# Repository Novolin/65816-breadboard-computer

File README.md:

# 65816-breadboard-computer
My Personal 65C816 breadboard build, including schematics, etc.

/KiCad contains my schematics/raw kicad files, if you want to laugh at my design.

/Software contains the programs I've written, mostly raw assembly, but I will hopefully have a C compiler up and running eventually.

/Docs will have a variety of documents on the exact nature of each hardware decision and how it works. I'll also be publishing these to a blog on my web zone. 

# Hardware Description:

This system is designed to use modular components, with room for expansion in RAM or I/O, using programmable logic. 

The primary CPU is a W65C816, which handles all logic/program execution. The "Bare Minimum" setup includes 32k of RAM and 32K of ROM space, both of which are placed on the primary controller board. The CPU is driven to 1 MHz by a divided clock oscillator, which provides a 2-phase clock signal, for any devices that may need it.

Expansion is handled through a 2x20 pin slot, so I can use a standard floppy drive cable to send it to a breakout board or other device.

## Graphical Output:

Despite my original intentions to use a z80 to drive a 320x240 display via weird magic bullshit, I have decided to switch to having the CPU directly control the display via the VIA's PORTB, though I will be sharing this with the 16x2 LCD thanks to some Ideas about how to handle I/O. See Docs/Displays for details.

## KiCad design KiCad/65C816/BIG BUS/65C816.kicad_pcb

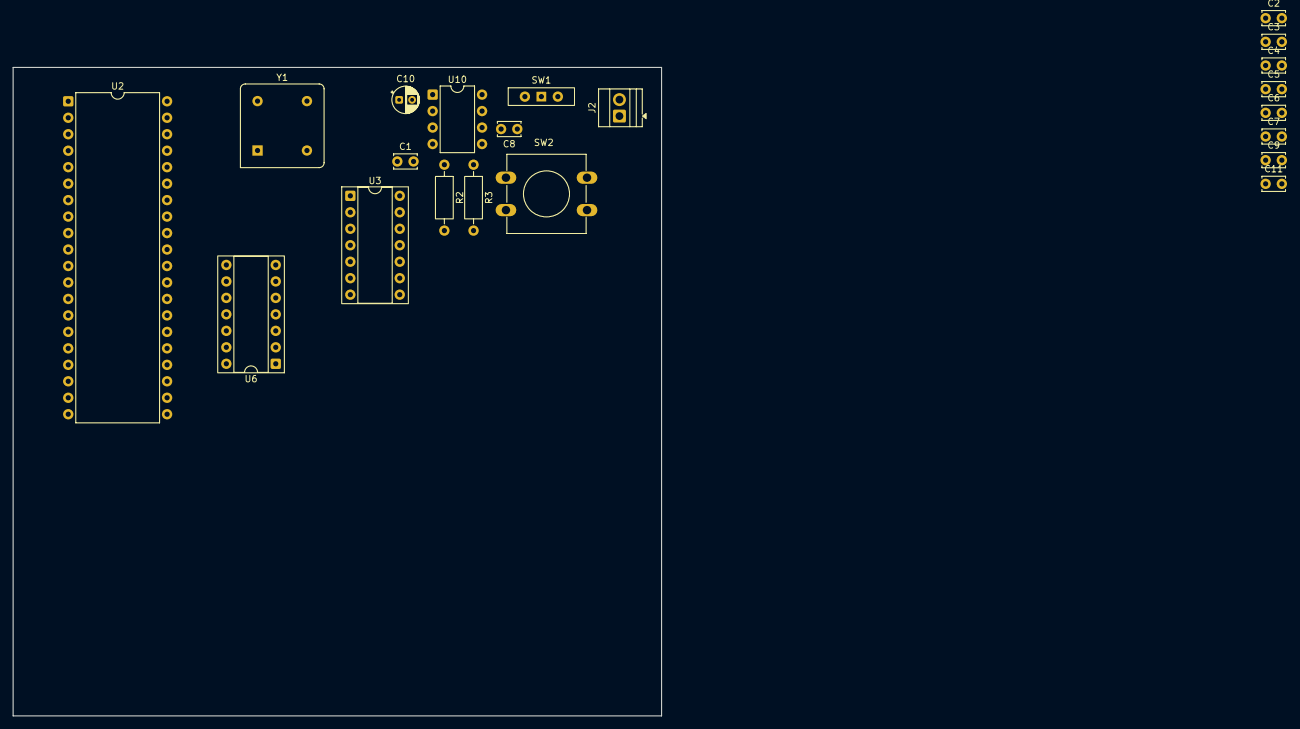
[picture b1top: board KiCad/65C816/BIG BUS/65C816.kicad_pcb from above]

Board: 2 copper layers, 100.0 x 100.0 mm, 21 parts (0 on the bottom side), 16 nets, no tracks yet.

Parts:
C1, C2, C3, C4, C5, C6, C7, C8, C9, C11: .1u; C_Disc_D3.4mm_W2.1mm_P2.50mm
C10: 2u; CP_Radial_D4.0mm_P2.00mm
J2: PWR IN; TerminalBlock_Xinya_XY308-2.54-2P_1x02_P2.54mm_Horizontal
R2: 10k; R_Axial_DIN0207_L6.3mm_D2.5mm_P10.16mm_Horizontal
R3: 1k; R_Axial_DIN0207_L6.3mm_D2.5mm_P10.16mm_Horizontal
SW1: PWR_SW; SW_Slide-03_Wuerth-WS-SLTV_10x2.5x6.4_P2.54mm
SW2: RESET; SW_PUSH-12mm
U2: W65C816SxP; DIP-40_W15.24mm
U3, U6: 74HC74; DIP-14_W7.62mm_Socket
U10: NE555P; DIP-8_W7.62mm
Y1: 16MHz; Oscillator_DIP-8

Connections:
+5V: C1.1, C2.1, C3.1, C4.1, C5.1, C6.1, C7.1, C9.1, C11.1, R2.2, R3.2, SW1.1 (B), U2.3 (~ABORT), U2.8 (VDD), U3.1 (~R), U3.4 (~S), U3.10 (~S), U3.13 (~R), U3.14 (VCC), U6.1 (~R), U6.4 (~S), U6.10 (~S), U6.13 (~R), U6.14 (VCC), U10.4 (R), U10.8 (VCC), Y1.1 (EN), Y1.8 (Vcc)
/CLK: U2.37 (ϕ0), U6.9 (Q)
/~CLK: U6.8 (~Q), U6.12 (D)
/~RESET: U2.40 (~RES), U10.3 (Q)
GND: C1.2, C2.2, C3.2, C4.2, C5.2, C6.2, C7.2, C8.1, C9.2, C10.2, C11.2, J2.1, SW2.1, U2.21 (VSS), U3.7 (GND), U6.7 (GND), U10.1 (GND), Y1.4 (GND)
unnamed: J2.2, SW1.3 (A)
unnamed: U3.3 (C), Y1.5 (OUT)
unnamed: U3.2 (D), U3.6 (~Q)
unnamed: U3.5 (Q), U3.11 (C)
unnamed: U3.8 (~Q), U3.12 (D)
unnamed: U3.9 (Q), U6.3 (C)
unnamed: U6.2 (D), U6.6 (~Q)
unnamed: U6.5 (Q), U6.11 (C)
unnamed: C8.2, U10.5 (CV)
unnamed: C10.1, R3.1, U10.6 (THR), U10.7 (DIS)
unnamed: R2.1, SW2.2, U10.2 (TR)

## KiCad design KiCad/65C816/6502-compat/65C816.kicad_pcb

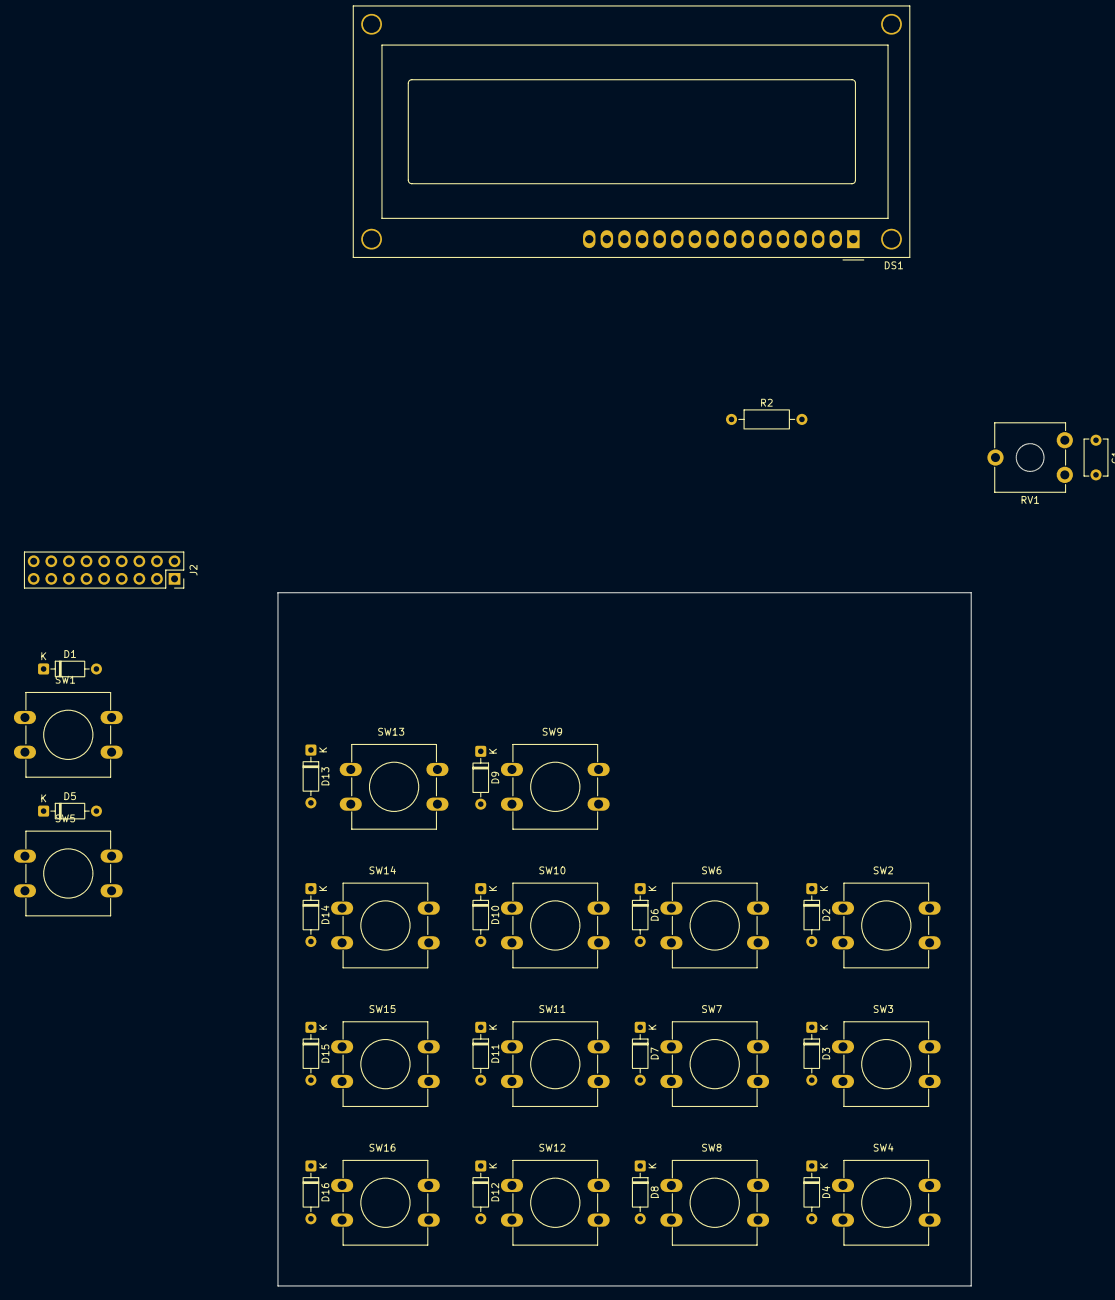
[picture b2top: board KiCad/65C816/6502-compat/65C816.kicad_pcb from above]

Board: 2 copper layers, 100.0 x 100.0 mm, 37 parts (0 on the bottom side), 35 nets, no tracks yet.

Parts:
C1: .1u; C_Disc_D5.1mm_W3.2mm_P5.00mm
D1, D2, D3, D4, D5, D6, D7, D8, D9, D10, D11, D12, D13, D14, D15, D16: D; D_DO-35_SOD27_P7.62mm_Horizontal
DS1: WC1602A
J2: Conn_02x09_Top_Bottom; PinSocket_2x09_P2.54mm_Vertical
R2: 680; R_Axial_DIN0207_L6.3mm_D2.5mm_P10.16mm_Horizontal
RV1: 1M; Potentiometer_ACP_CA9-V10_Vertical_Hole
SW1: A1; SW_PUSH-12mm
SW2: B1; SW_PUSH-12mm
SW3: C1; SW_PUSH-12mm
SW4: D1; SW_PUSH-12mm
SW5: A2; SW_PUSH-12mm
SW6: B2; SW_PUSH-12mm
SW7: C2; SW_PUSH-12mm
SW8: D2; SW_PUSH-12mm
SW9: A3; SW_PUSH-12mm
SW10: B3; SW_PUSH-12mm
SW11: C3; SW_PUSH-12mm
SW12: D3; SW_PUSH-12mm
SW13: A4; SW_PUSH-12mm
SW14: B4; SW_PUSH-12mm
SW15: C4; SW_PUSH-12mm
SW16: D4; SW_PUSH-12mm

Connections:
+5V: C1.2, DS1.2 (VDD), DS1.15 (LED(+)), J2.10, RV1.3
GND: C1.1, DS1.1 (VSS), J2.1, R2.1, RV1.1
unnamed: D1.2 (A), SW1.2
unnamed: D1.1 (K), D5.1 (K), D9.1 (K), D13.1 (K), J2.6
unnamed: D2.2 (A), SW2.2
unnamed: D3.2 (A), SW3.2
unnamed: D4.2 (A), SW4.2
unnamed: D5.2 (A), SW5.2
unnamed: D6.2 (A), SW6.2
unnamed: D7.2 (A), SW7.2
unnamed: D8.2 (A), SW8.2
unnamed: D9.2 (A), SW9.2
unnamed: D10.2 (A), SW10.2
unnamed: D2.1 (K), D6.1 (K), D10.1 (K), D14.1 (K), J2.7
unnamed: D11.2 (A), SW11.2
unnamed: D3.1 (K), D7.1 (K), D11.1 (K), D15.1 (K), J2.8
unnamed: D12.2 (A), SW12.2
unnamed: D4.1 (K), D8.1 (K), D12.1 (K), D16.1 (K), J2.9
unnamed: D13.2 (A), SW13.2
unnamed: D14.2 (A), SW14.2
unnamed: D15.2 (A), SW15.2
unnamed: D16.2 (A), SW16.2
unnamed: DS1.11 (D4), J2.15
unnamed: DS1.12 (D5), J2.16
unnamed: DS1.13 (D6), J2.17
unnamed: DS1.14 (D7), J2.18
unnamed: DS1.6 (E), J2.11
unnamed: DS1.16 (LED(-)), R2.2
unnamed: DS1.4 (RS), J2.13
unnamed: DS1.5 (R/W), J2.12
unnamed: DS1.3 (VO), RV1.2
unnamed: J2.2, SW1.1, SW2.1, SW3.1, SW4.1
unnamed: J2.3, SW5.1, SW6.1, SW7.1, SW8.1
unnamed: J2.4, SW9.1, SW10.1, SW11.1, SW12.1
unnamed: J2.5, SW13.1, SW14.1, SW15.1, SW16.1

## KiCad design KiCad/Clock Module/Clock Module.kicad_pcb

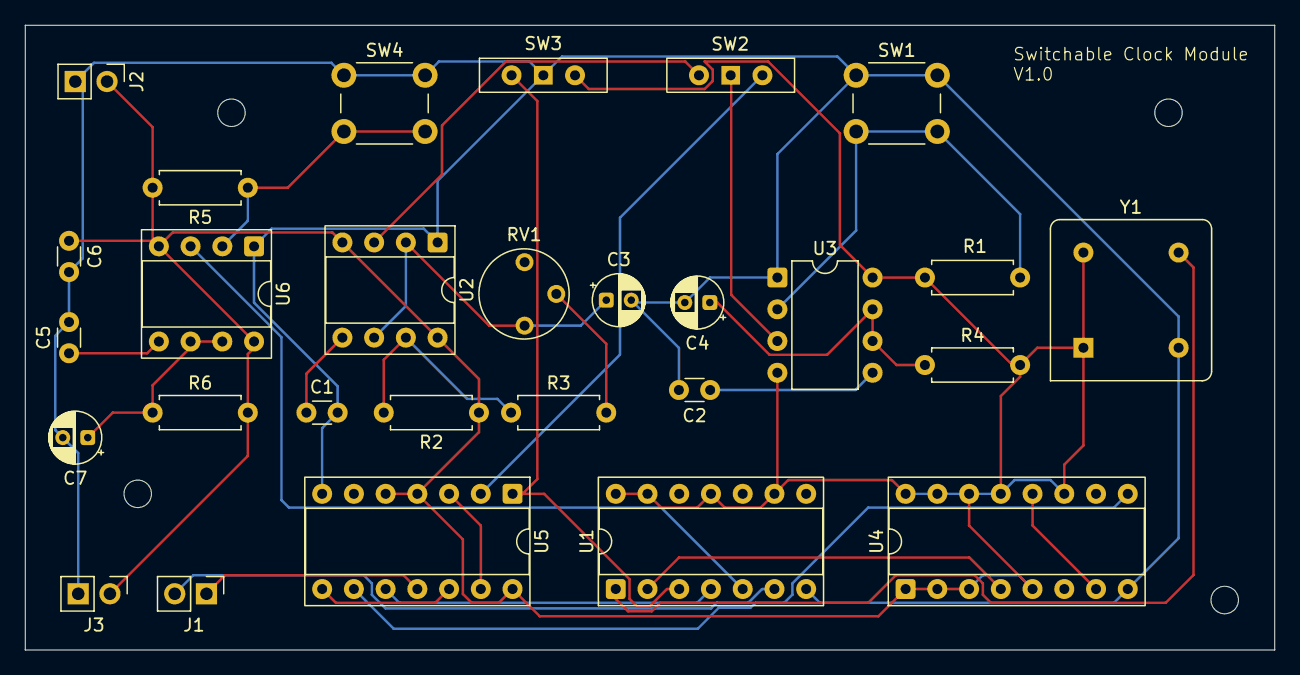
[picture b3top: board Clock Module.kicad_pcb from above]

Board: 2 copper layers, 100.0 x 50.0 mm, 28 parts (0 on the bottom side), 26 nets.

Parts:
C1, C2, C5, C6: .1u; C_Disc_D3.0mm_W1.6mm_P2.50mm
C3: .22u; CP_Radial_D4.0mm_P2.00mm
C4, C7: 3.3u; CP_Radial_D4.0mm_P2.00mm
J1: RESET/CLK; PinHeader_1x02_P2.54mm_Vertical
J2: PWR IN; PinHeader_1x02_P2.54mm_Vertical
J3: PWR OUT; PinHeader_1x02_P2.54mm_Vertical
R1, R2, R3, R4, R5, R6: 1k; R_Axial_DIN0207_L6.3mm_D2.5mm_P7.62mm_Horizontal
RV1: 50k; Potentiometer_Vishay_T7-YA_Single_Vertical
SW1: Manual Clock; SW_PUSH_6mm
SW2: SLOW/MAN; SW_Slide-03_Wuerth-WS-SLTV_10x2.5x6.4_P2.54mm
SW3: CLK_SEL; SW_Slide-03_Wuerth-WS-SLTV_10x2.5x6.4_P2.54mm
SW4: Reset; SW_PUSH_6mm_H13mm
U1: 74HC14; DIP-14_W7.62mm_Socket
U2: 555 Clock; DIP-8_W7.62mm_Socket
U3: Manual Debounce; DIP-8_W7.62mm
U4: 74LS109; DIP-16_W7.62mm_Socket
U5: 74LS00; DIP-14_W7.62mm_Socket
U6: Reset Debounce; DIP-8_W7.62mm_Socket
Y1: CXO_DIP8; Oscillator_DIP-8

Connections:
+5V: C6.1, J2.1, J3.1, R1.2, R2.1, R4.2, R5.2, R6.2, SW3.3 (C), U1.9, U1.11, U1.13, U1.14 (VCC), U2.4 (R), U2.8 (VCC), U3.4 (R), U3.8 (VCC), U4.1 (~R), U4.2 (J), U4.3 (~K), U4.5 (~S), U4.11 (~S), U4.13 (~K), U4.14 (J), U4.15 (~R), U4.16 (VCC), U5.4, U5.5, U5.14 (VCC), U6.4 (R), U6.8 (VCC), Y1.1 (EN), Y1.8 (Vcc)
Clock: J1.1, U5.11
Fast Clock: U4.9 (~Q), U5.9
GND: C1.2, C2.2, C3.2, C4.2, C5.2, C6.2, C7.2, J2.2, J3.2, SW1.1, SW3.1 (A), SW4.1, U1.7 (GND), U2.1 (GND), U3.1 (GND), U4.8 (GND), U5.7 (GND), U6.1 (GND), Y1.4 (GND)
unnamed: R3.2, RV1.2
unnamed: SW2.1 (A), U3.3 (Q)
unnamed: SW2.2 (B), U5.2
unnamed: SW3.2 (B), U1.3, U5.1
unnamed: U1.4, U5.10
unnamed: C1.1, U2.5 (CV)
unnamed: R2.2, R3.1, U2.7 (DIS)
unnamed: C3.1, RV1.1, U2.2 (TR), U2.6 (THR)
unnamed: C2.1, U3.5 (CV)
unnamed: C4.1, R4.1, U3.6 (THR), U3.7 (DIS)
unnamed: R1.1, SW1.2, U3.2 (TR)
unnamed: U1.2, U4.4 (C)
unnamed: U4.7 (~Q), U4.12 (C)
unnamed: U5.8, U5.12
unnamed: U5.3, U5.13
unnamed: C5.1, U6.5 (CV)
unnamed: C7.1, R6.1, U6.6 (THR), U6.7 (DIS)
unnamed: U1.5, U6.3 (Q)
unnamed: R5.1, SW4.2, U6.2 (TR)
unnamed: U1.1, Y1.5 (OUT)
Reset: J1.2, U1.6
Slow Clock: SW2.3 (C), U2.3 (Q)

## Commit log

2025-08-26 Added local files
2025-08-27 fixed typo causing control signals to never send.
2025-09-02 started eeprom programmer stuff
2025-09-02 Uploaded data sheets, did some more programmer stuff. Also some assembly stuff.
2025-09-27 Working on programmer stuff
2025-11-07 Rewrite of the programmer to make it make more sense to me.
2025-11-07 docs
2025-11-08 syncing some changes from my laptop
2025-11-08 Tweaked programmer stuff, hopefully it works.
2025-11-08 what the fuck was i on when i wrote that first asm lmao
2025-11-15 i think this is better idk
2025-11-25 started documenting GPU stuff.
2025-11-25 Whole bunch of stuff, removed EEPROM writer (i bought one sorry) and hella schematic changes
2025-11-27 Preliminary PLD stuff, state machines are scary
2025-12-02 lots of stiff
2025-12-02 aaaaaaa
2025-12-17 reconfigured to make getting anything to work a little easier. writing new asm.
2025-12-17 Cleaned up random files, added actual .gitignore on my end lmao
2025-12-17 updated ignore list
2025-12-17 removed serial adapter code - will use a different interface!!
2025-12-23 Switched from vasm for compilation to CC65, since it has better '816 support, and I can start using C.
2025-12-27 started re-re-re-redoing hello world, this time properly doing the lcd stuff.
2025-12-27 fart asses.
2025-12-29 i thikn ive figured it out but i gotta try
2025-12-31 I did not, in fact, figure it out.
2026-01-02 Started writing proper code with includes and shit, but we'll see if i can even get code to run lol
2026-01-02 forgot to stage this one too
2026-01-02 Finished init code, I think?
2026-01-03 removed some old files, started building code for a full-ass system!
2026-01-04 Schematic updates
2026-01-05 missed a "#" so it would never check a busy flag.
2026-01-05 started rewriting lcd stuff to include graphical display!
2026-01-06 Renamed, docs, preparing for keypad integration
2026-01-06 more lcd work
2026-01-07 dog i forgot to rts the startup sub.
2026-01-07 i dont trust like that so imade omethine use x
2026-01-10 fixed another bug, made a build script
